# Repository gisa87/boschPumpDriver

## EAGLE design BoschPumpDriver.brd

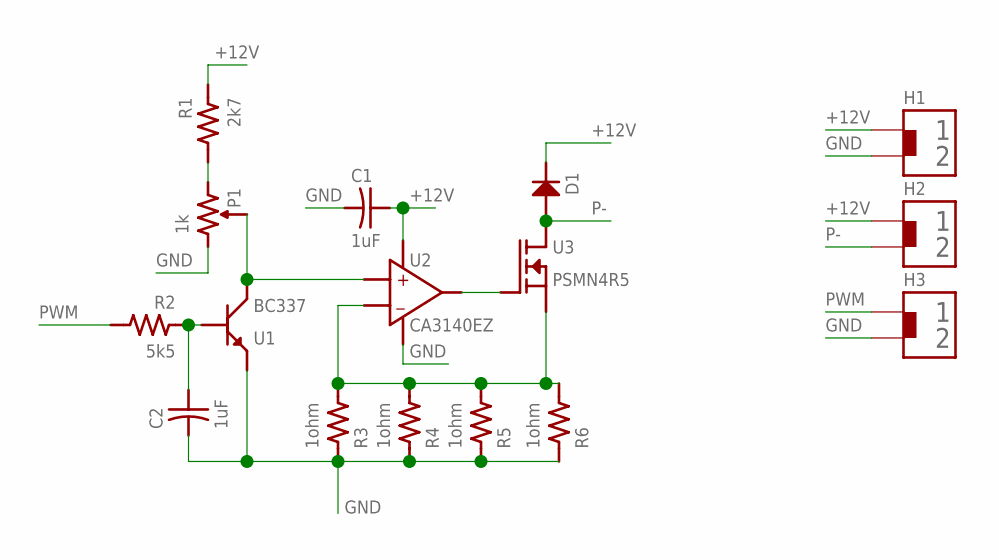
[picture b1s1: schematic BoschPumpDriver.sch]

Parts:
C1, C2: 1uF; CRS100NF
D1: DIODEVERT; R_VERT
H1: VCC; HEADER2PIN
H2: PUMP; HEADER2PIN
H3: PWM; HEADER2PIN
P1: 1k; 3PIN_POT_2.54
R1: 2k7; R1/4TH
R2: 5k5; R_VERT
R3, R4, R5, R6: 1ohm; R_VERT
U1: BC337; TO92
U2: CA3140EZ; DIP8
U3: PSMN4R5; TO-220

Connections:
+12V: C1.+, D1.2 (OUT), H1.1, H2.1, R1.P$1, U2.7 (VCC+)
GND: C1.-, C2.-, H1.2, H3.2, P1.1, R3.1, R4.1, R5.1, R6.1, U1.3 (E), U2.4 (VCC-)
unnamed: U2.6 (OUT), U3.1 (G)
unnamed: P1.2, U1.1 (C), U2.3 (IN+)
unnamed: C2.+, R2.1, U1.2 (B)
unnamed: R3.2, R4.2, R5.2, R6.2, U2.2 (IN-), U3.3 (S)
unnamed: P1.3, R1.P$2
P-: D1.1 (IN), H2.2, U3.2 (D)
PWM: H3.1, R2.2

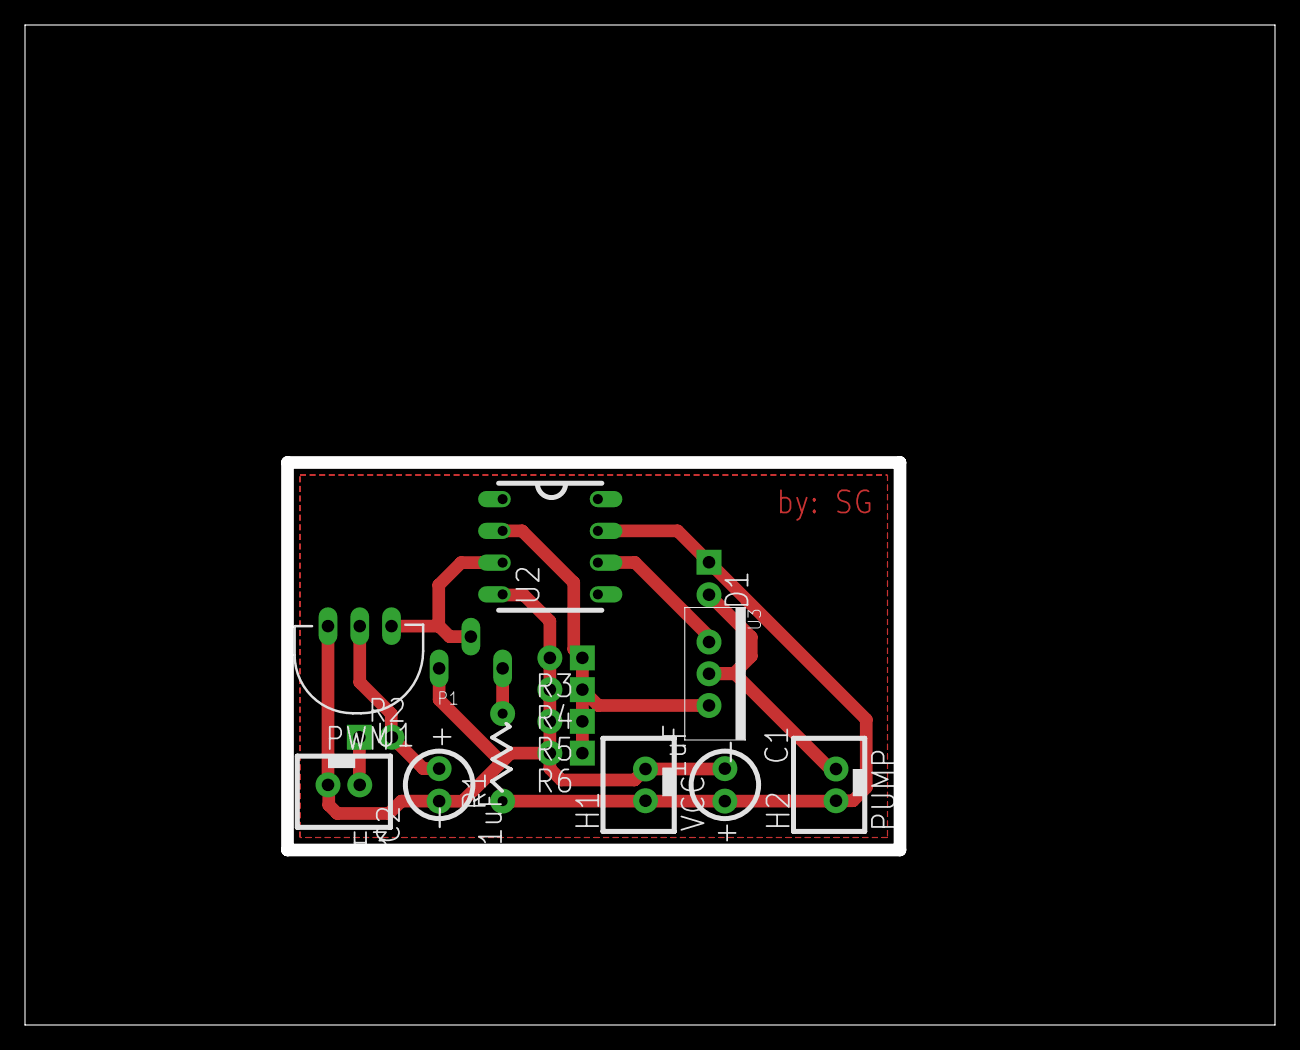
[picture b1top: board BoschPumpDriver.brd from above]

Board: 2 copper layers, 100.0 x 80.0 mm, 16 parts (0 on the bottom side), 9 nets.

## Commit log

2017-09-01 CreatedProject
2017-09-04 Board updated
